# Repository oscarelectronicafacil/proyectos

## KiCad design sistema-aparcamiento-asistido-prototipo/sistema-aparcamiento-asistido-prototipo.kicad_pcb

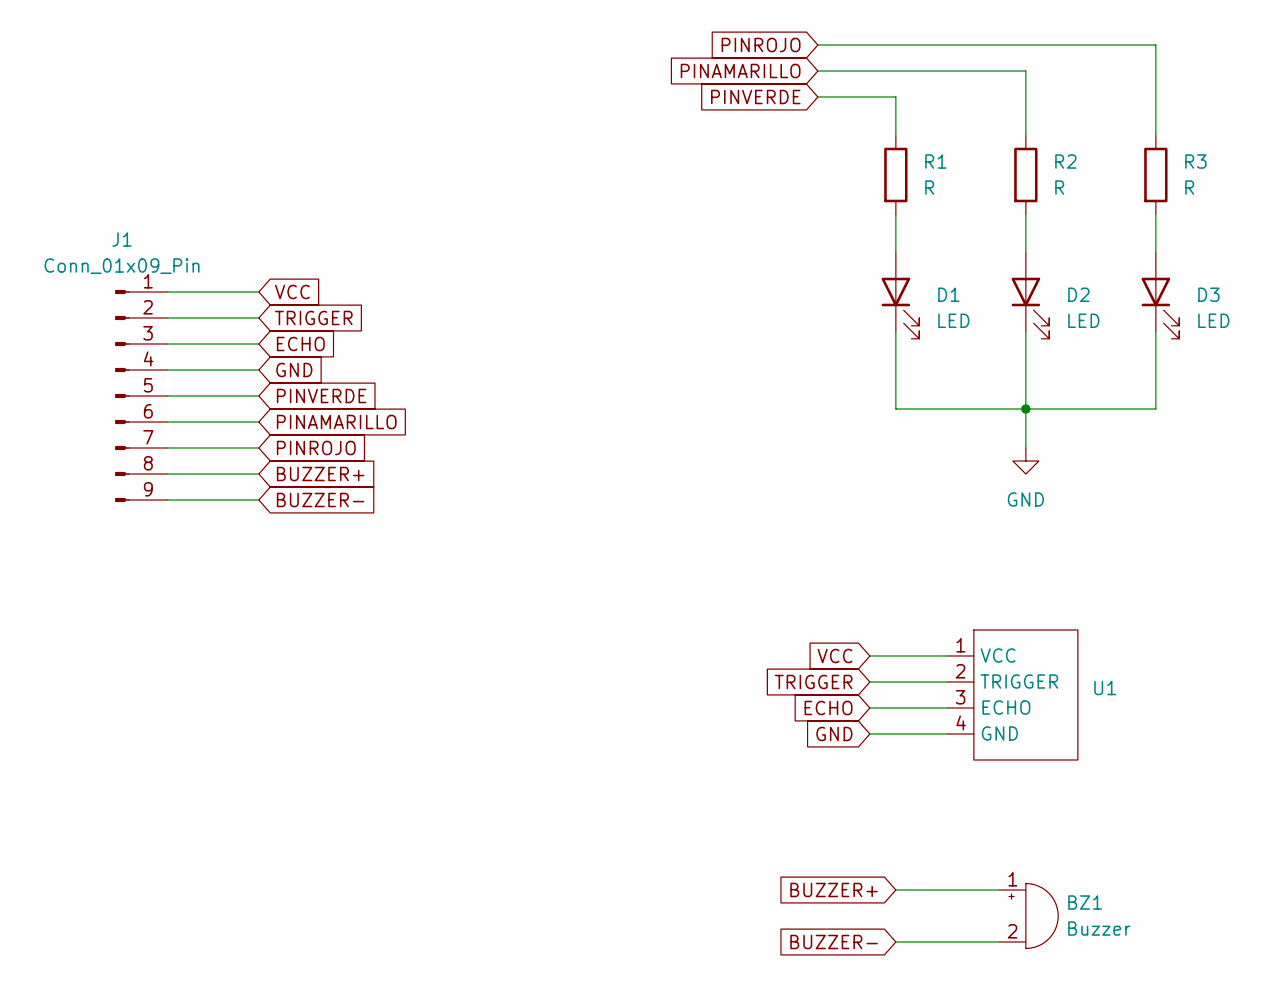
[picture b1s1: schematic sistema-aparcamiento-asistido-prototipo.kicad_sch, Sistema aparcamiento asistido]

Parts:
BZ1: Buzzer; PhoenixContact_MCV_1,5_2-G-3.5_1x02_P3.50mm_Vertical
D1, D2, D3: LED; LED_D5.0mm
J1: Conn_01x09_Pin; PhoenixContact_MCV_1,5_9-G-3.5_1x09_P3.50mm_Vertical
R1, R2, R3: R; R_Axial_DIN0204_L3.6mm_D1.6mm_P7.62mm_Horizontal
U1: PhoenixContact_MCV_1,5_4-G-3.5_1x04_P3.50mm_Vertical

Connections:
BUZZER+: BZ1.1 (+), J1.8
BUZZER-: BZ1.2 (-), J1.9
ECHO: J1.3, U1.3 (ECHO)
GND: D1.1 (K), D2.1 (K), D3.1 (K), J1.4, U1.4 (GND)
unnamed: D1.2 (A), R1.2
unnamed: D2.2 (A), R2.2
unnamed: D3.2 (A), R3.2
PINAMARILLO: J1.6, R2.1
PINROJO: J1.7, R3.1
PINVERDE: J1.5, R1.1
TRIGGER: J1.2, U1.2 (TRIGGER)
VCC: J1.1, U1.1 (VCC)

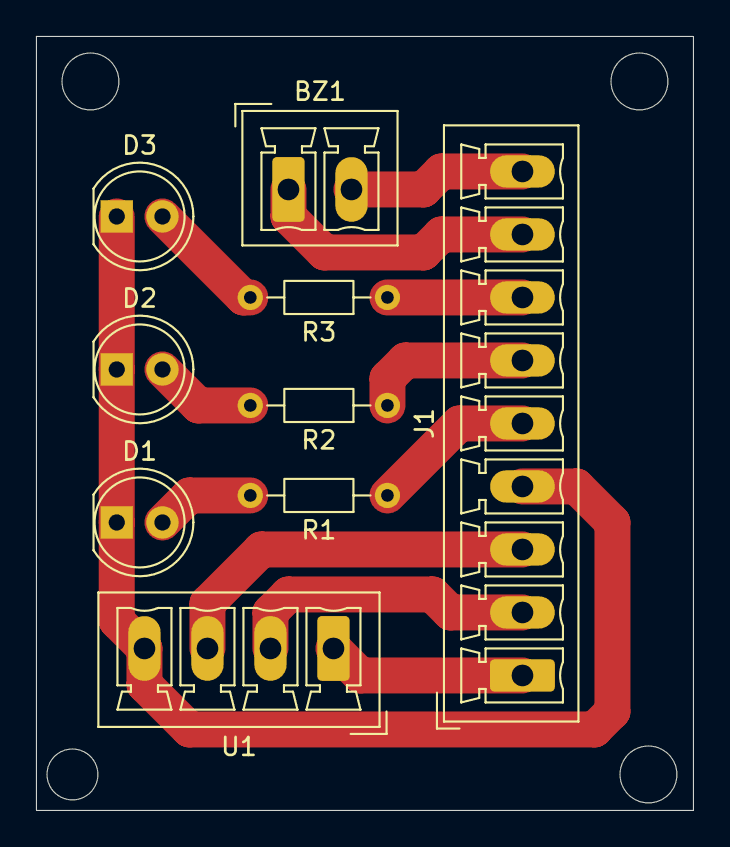
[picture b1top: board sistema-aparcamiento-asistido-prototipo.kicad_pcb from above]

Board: 2 copper layers, 36.5 x 43.0 mm, 9 parts (0 on the bottom side), 12 nets.
